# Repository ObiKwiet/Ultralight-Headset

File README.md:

# Ultralight Headset
This is a project to make a better communications headset for ultralights, but specifically for paramotors. 

## Goals
- Modularity - Everyone's needs and budget are a little different, so we want to make it possible put together certain features a la carte.
- ANR - Active noise cancelation modules are rare for UL headsets, but they are the only way of effectively attenuating the low frequencies generated by our two stroke engines and prop. 
- Wireless links - The helmet itself should have a wireless link to other system components. Reducing the number of wires around us is not only convenient, but also an important safety improvement. This should also reduce cost and labor by eliminating a complex cable assembly, and expensive connectors.
- Radio connectivity - The system should accommodate at least two simultaneous analog radios, cell phone connectivity, and bluetooth intercom.  
- Side tone - The system should feed the microphone signal back into the speakers for the comfort of the user. 

## Roadmap
The roadmap lays out the requirements for each version of the headset along its development. 

### Version 1.0

Version 1 and its derivatives have a fully wired interface between all modules. The first version supports a single radio, and audio input from an AUX jack. 

### Version 1.1

Version 1.1 will change the following items.

- Side tone support. Side tone plays audio from the microphone back through the speakers to allow the user to hear themselves speak. The greatly improves the comfort of speaking. 

- A generic pigtail drawing will be added so cable for arbitrary radios can easily be constructed. 

### Version 2.0

Version 2.0 will involve a major redesign, and significantly increase the design complexity of the headset. However, it should hopefully reduce overall cost and build difficulty. 

The following things will be completed for 2.0:

- The link between the IO Module and the Headset will be changed to a bluetooth interface. 

- The IO Module Case will be changed, and support for one additional analog radio will be added. 

- The connecters may be changed to reduce cost. 

- The radio toggle interface will need to be changed

- Support for Senna intercom may be added in a subversion.

- Throttle PTT will be added, but may be pushed to 2.1

- A battery will be added to the headset. 

- The microphone on the headset will change to a more robust aviation style

- Microphone input will be added to the aux jack

## Drawing Numbering and Style Guide

This is still WIP. For now I am trying to use a formal drawing tree. Drawings from various CAD softwares are printed to PDF and controlled in the Git repository, and source files will be kept in their own folder. Configuration management is TBD, but for the most part we will just add dash numbers to drawings of major changes to systems. 
Minor changes will be reflected by a change in the revision letter.  I will need to set up some configuration management spreadsheet to identify which dash numbers go into each version.  

## CAD Software 
Currently, Fusion360 is being used for mechanical CAD. Due to major shortcomings with the drafting module, it would be desirable to move to Solidworks. Solidworks is normally very expensive but is available through the EAA for use on open source projects. 
In the meantime, I'd be happy to add you to the Fusion360 project if you email me. There isn't any obvious way to link to it as a public repo.

Certain drawings are maintained on sheets, which has the advantage of being free, and the major disadvantage of not having version control synced with the repository. 
- [Wirelists for A1300](https://docs.google.com/spreadsheets/d/1odUo59O54lUUatiMipqJTk2xvd_l8rzADcac63PmRdw/edit?usp=sharing)
- [Partlists](https://docs.google.com/spreadsheets/d/1oErzroamnteU2tq9hoaM70eOOeuBpsWLLE8QT7xZNOo/edit?usp=sharing)
- [Drawing Tree](https://docs.google.com/spreadsheets/d/1H3n_jioX6qo1rZ_G6kWBhMTz45Bp03Awh5uix86TeiI/edit?usp=sharing)

KiCad will be used for electrical schematics and PCBs. 

Currently, we don't really have proper wiring diagrams, but these will probably be done with AutoCad electrical, due to a total lack of free software to do the job. There aren't any reasonably priced ways to get AutoCad unless you are a student, so finding a work around will be up to you. 

## Assembly Guide

I was going to write up a detailed assembly guide, but at this point the project isn't really in a solid enough state to be used by someone who can't figure it out well enough from the drawings. This will have to wait for 2.0. 

## Pictures

These are some images of the 1.0 version.

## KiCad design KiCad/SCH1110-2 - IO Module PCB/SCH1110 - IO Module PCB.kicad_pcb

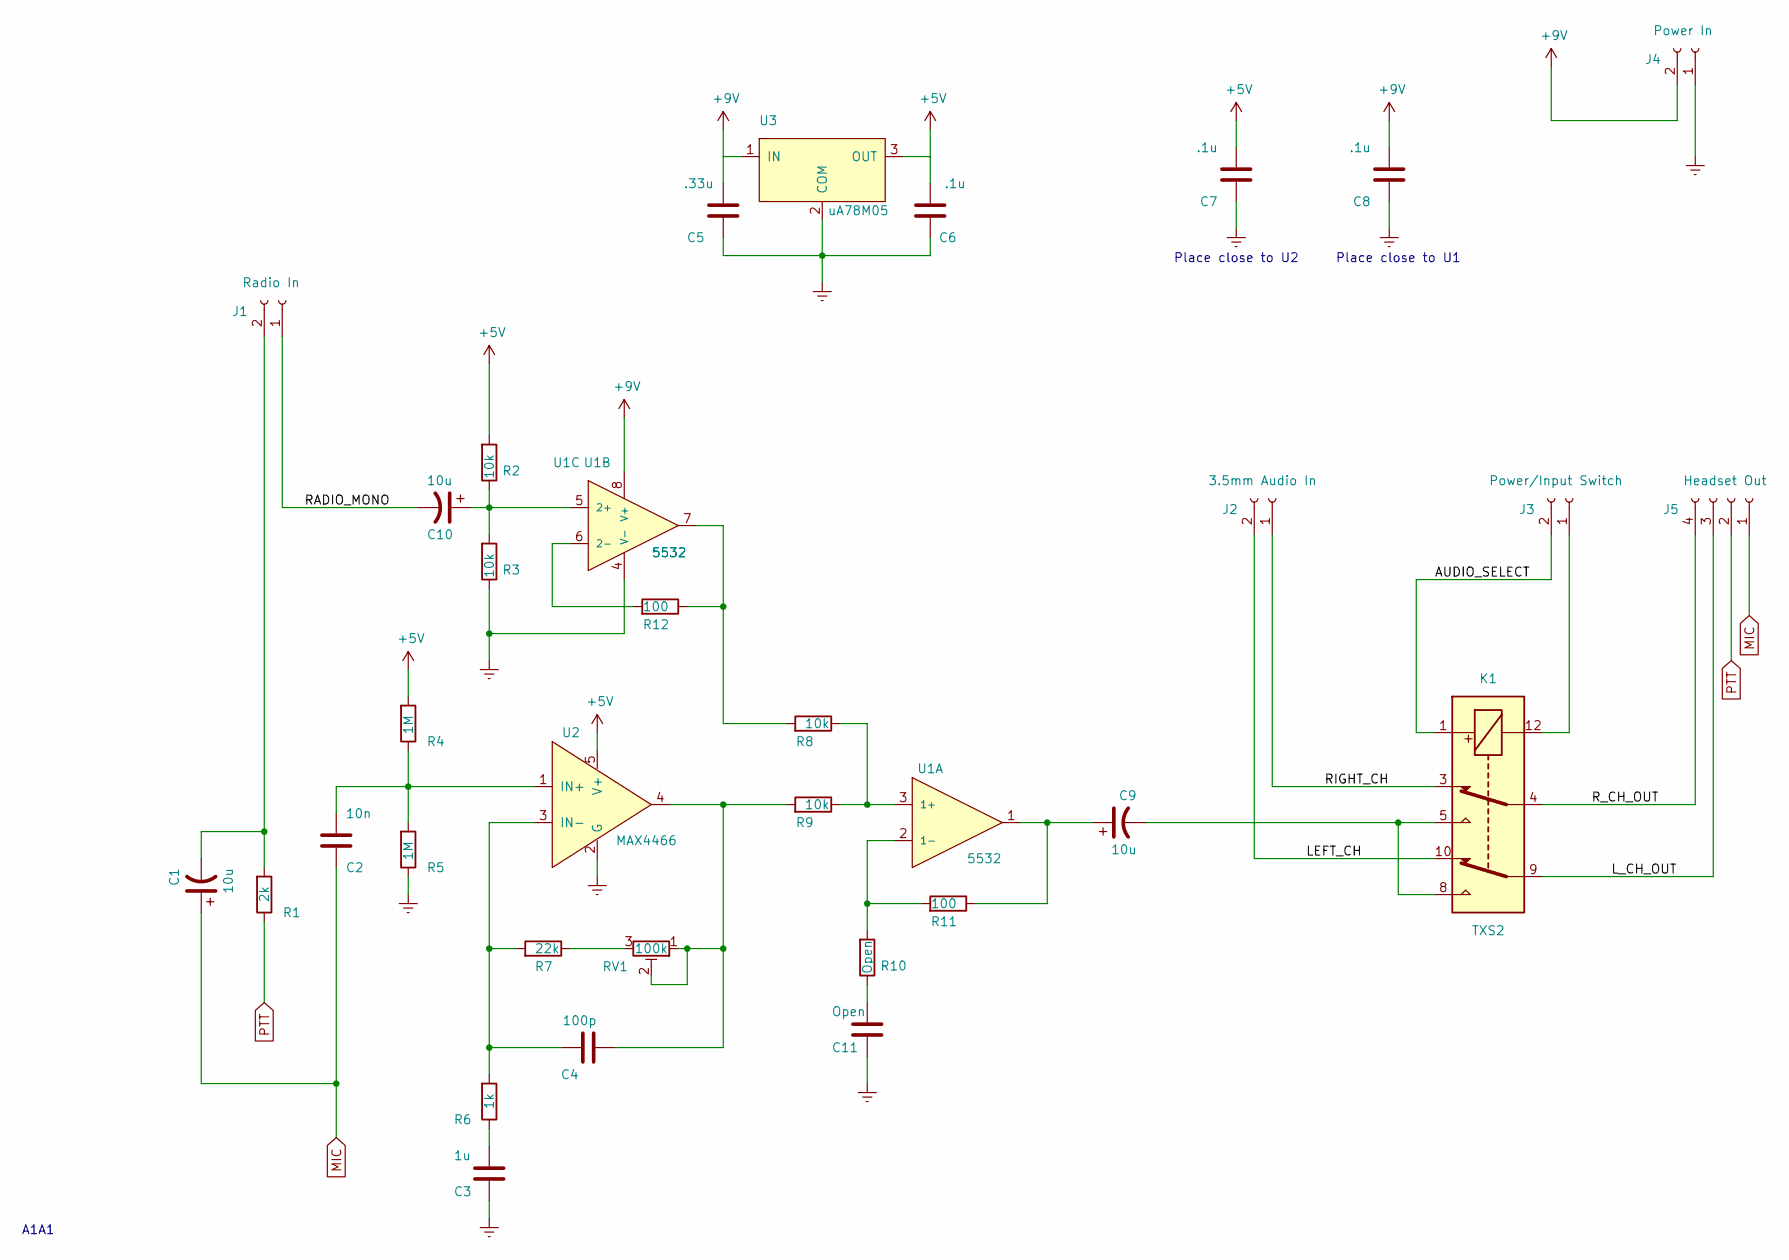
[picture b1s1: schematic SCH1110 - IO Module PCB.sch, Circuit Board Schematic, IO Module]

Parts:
C1, C9, C10: 10u; CP_Radial_D6.3mm_P2.50mm
C2: 10n; 0603
C3: 1u; 0805
C4: 100p; 0603
C5: .33u; 0805
C6, C7, C8: .1u; 0603
C11: Open; 0805
J1: Radio In; WP-75mil-1x02
J2: 3.5mm Audio In; WP-75mil-1x02
J3: Power/Input Switch; WP-75mil-1x02
J4: Power In; WP-75mil-1x02
J5: Headset Out; WP-75mil-1x04
K1: TXS2; TXS2-THT
R1: 2k; 0603
R2, R3, R8, R9: 10k; 0603
R4, R5: 1M; 0603
R6: 1k; 0603
R7: 22k; 0603
R10: Open; 0603
R11, R12: 100; 0603
RV1: 100k; Potentiometer_Bourns_3224X_Vertical
U1: 5532; SOIC-8_W3.9mm
U2: MAX4466; SOT-353
U3: uA78M05; Trans_SOT-223-4

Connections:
+5V: C6.2, C7.2, R2.2, R4.2, U2.5 (V+), U3.3 (OUT)
+9V: C5.2, C8.2, J4.2, U1.8 (V+), U3.1 (IN)
/AUDIO_SELECT: J3.2, K1.1
/LEFT_CH: J2.2, K1.10
/L_CH_OUT: J5.3, K1.9
/RADIO_MONO: C10.2, J1.1
/RIGHT_CH: J2.1, K1.3
/R_CH_OUT: J5.4, K1.4
Earth: C3.2, C5.1, C6.1, C7.1, C8.1, C11.2, J4.1, R3.1, R5.1, U1.4 (V-), U2.2 (G), U3.2 (COM)
MIC: C1.1, C2.2, J5.1
unnamed: C1.2, J1.2, R1.2
unnamed: C2.1, R4.1, R5.2, U2.1 (IN+)
unnamed: C3.1, R6.1
unnamed: C4.1, R6.2, R7.2, U2.3 (IN-)
unnamed: C4.2, R9.2, RV1.1, RV1.2, U2.4
unnamed: C9.1, R11.1, U1.1
unnamed: C9.2, K1.5, K1.8
unnamed: C10.1, R2.1, R3.2, U1.5 (2+)
unnamed: C11.1, R10.1
unnamed: J3.1, K1.12
unnamed: R7.1, RV1.3
unnamed: R8.1, R9.1, U1.3 (1+)
unnamed: R10.2, R11.2, U1.2 (1-)
unnamed: R8.2, R12.1, U1.7
unnamed: R12.2, U1.6 (2-)
PTT: J5.2, R1.1

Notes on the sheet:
A1A1
Place close to U2
Place close to U1

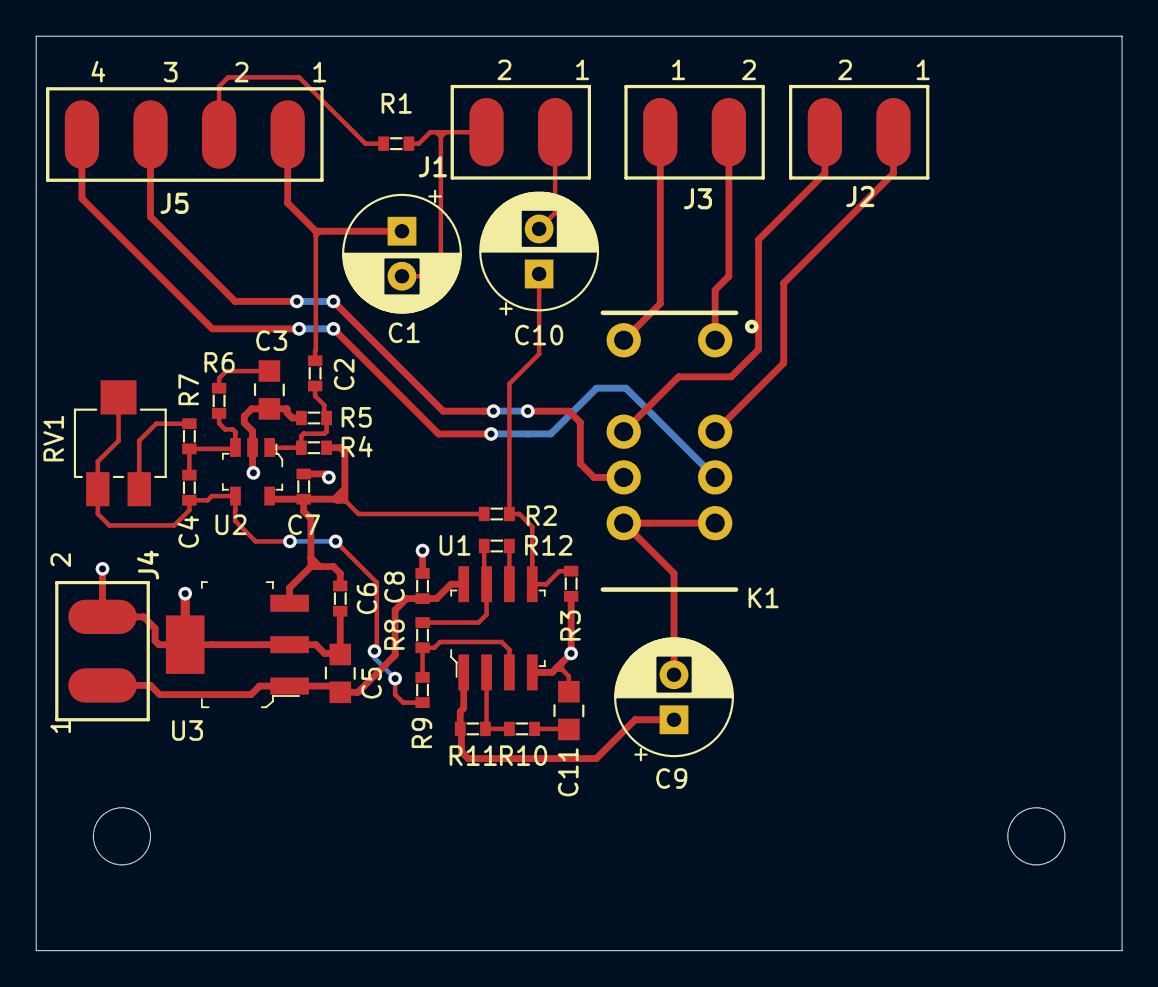
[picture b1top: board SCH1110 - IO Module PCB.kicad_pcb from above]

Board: 2 copper layers, 60.3 x 50.8 mm, 33 parts (0 on the bottom side), 26 nets.

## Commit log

2019-03-18 Initial Commit of Files
    Rev A as built of first prototype.
2019-03-18 Started Basic Read Me
2019-03-20 Added system block diagram.
2019-04-04 Updated Readme, added Docs folder.
2019-04-04 Uploaded pics of version 1.0
2019-04-04 Fixed picture file extensions.
2019-04-12 Added SCH1110-2
2019-04-15 Review changes and adjustments
2019-04-15 Final for this rev. Added gerbers and drills.
2019-06-02 Incorporated redlines for -2 PCB and wiring schematics.
